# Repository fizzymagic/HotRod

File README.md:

# HotRod
HotRod game controller adapter to USB

## Introduction

This project allows use of a HotRod SE controller with a modern computer.  It also adds considerable 
flexibility, allowing you to remap the HotRod controls to any keys on the keyboard with *no* driver 
configuration on your PC.  Since the device emulates a USB HID keyboard, it will work with any OS that
can use the keyboard, including Windows, Mac OS, and Linux.

## Requirements

Getting the entire thing working requires:

- 32u4-based arduino clone.  I recommand the Pololu A-Star series, but it should work with any 32u4-based board.
  - The Arduino needs a Caterina (or equivalent) bootloader in it.  The Arduino Micro and the A-Star both have this as the default.
- Arduino 1.6.9 or later IDE
- A 6-pin female mini DIN connecter (aka a PS/2 keyboard connector)
- A completed circuit board with the appropriate wires from the DIN connector to the Arduino.  
  You can get a board from OSH Park
- Python 2.7.9 or later.
  - The pyserial library must be installed on the system.

## Getting Started

1. Wire the PS/2 connector to the Arduino, or populate the board.
  - The board design is in the **Hardware/** folder.
  - The board can be obtained from OSH Park [here](https://oshpark.com/shared_projects/7dNfPtaw) 
2. Copy the **HotRod/** folder into the Arduino **libraries/** folder in your Arduino user space. 
   If necessary, you may need to create the **libraries** folder.
3. Copy the **HotRodtoUSB/** folder into the Arduino user space.
4. Copy the **HotRodSetup/** folder into some other place on your computer.  It doesn't really
   matter where.
5. Compile and upload the HotRodtoUSB sketch to the Arduino.
   
## Using the HotRod-to-USB adapter

## Using SetupHotRod.py

This Python script will automatically send commands to the HotRod interface from a file.  You can
save various configurations in command files to quickly load new controller configurations.

You will need Python 2.7.9 or later, with the ```pyserial``` library installed.

### Command Line

<pre>python SetupHotRod.py [-p portname] [-s] [-d] [-r] [cmdFile] ...
         cmdFile  Name of one or more serial commands file(s).  Not required.
         -p  specify serial port, e.g. COM3 for Windows, /dev/ttyS2 for linux and Mac
             if not specified port will be autodetected
         -s  save mapping to EEPROM after processing file
         -d  dump current mapping after processing file
         -r  reset mapping to default before processing file
         -l  reinitialize mapping from EEPROM before processing file</pre>

### Serial Command Set

The following commands are available to be sent to the HotRod interface from SetupHotRod.py; the input file
should consist of one command per line.

- **M sc kb**: Map scan code *sc* to  keyboard key *kb*
  - The scan code and keyboard key can be specified in ways:
    1. As a macro (all macros are defined in HotRod.py)
    2. As a 2-digit hexadecimal number
  - Additionally, the keyboard key can be specified:
    3. As an ASCII character
- **S**: Save the current key mapping to EEPROM
- **R**: Reset the key mapping to the original (in PROGMEM)
- **L**: Load a key mapping from EEPROM
- **D**: Dump the current key mapping
- **?**: Echo "HotRod" to serial port

### Examples:

```M HR_LEFT_JOYSTICK_UP KB_UP_ARROW```  
Maps the left joystick up to the keyboard up arrow.

```M 75 DA```  
Also maps the left joystick up to the keyboard up arrow.

```M HR_LEFT_JOYSTICK_UP i```  
Maps the left joystick up to ASCII 'i'

### Included command files

- SE_MAME_default.hrm
  - Default MAME configuration for 2 players.
- SE_MAME_2joy.hrm
  - Default MAME configuration for 2-joystick games.

## Additional Information

### Pin setup:

```
DIN-6 Pin    Arduino Pin
   1             D2
   3             GND
   4             +5V
   5             D3
```

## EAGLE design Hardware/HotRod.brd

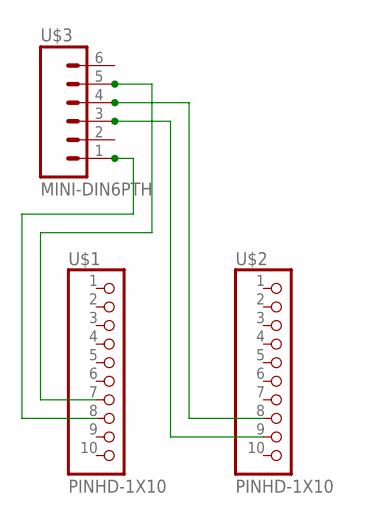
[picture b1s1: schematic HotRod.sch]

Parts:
U$1, U$2: PINHD-1X10; 1X10-BIG
U$3: MINI-DIN6PTH; MINI-DIN6

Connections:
unnamed: U$1.8, U$3.1
unnamed: U$1.7, U$3.5
unnamed: U$2.8, U$3.4
unnamed: U$2.9, U$3.3

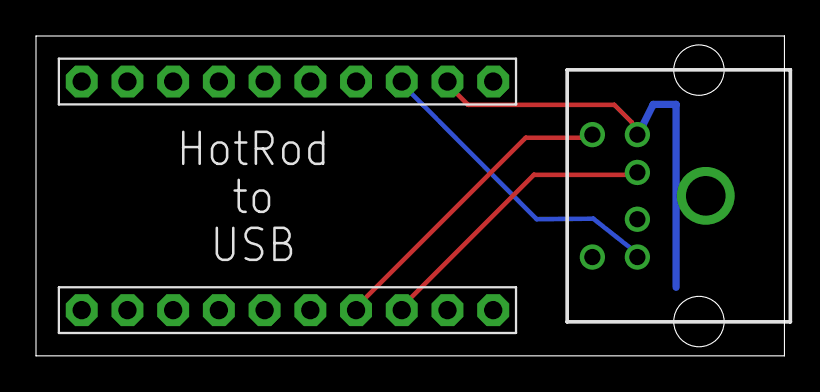
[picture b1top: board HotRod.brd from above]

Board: 2 copper layers, 41.6 x 17.8 mm, 3 parts (0 on the bottom side), 4 nets.

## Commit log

2016-09-04 Added Python to detect HotRod
2016-09-04 Fixed minor bugs
2016-09-04 Minor edit to test git
2016-09-04 Added example MAME deafult file.
2016-09-04 Threads for port detection working. Python to send keymap working.
2016-09-06 Modified Hotrod to allow either uppercase or lowercase characters to be sent.
2016-09-07 Added new map files; cleaned up Arduino project to work with newest IDE.
2016-09-08 Minor modifications to library and timing put into sketch (temporary)
2016-09-09 More additional documentation
2016-09-09 Added Hardware folder
2016-09-26 Added new key files and new key definitions
2016-10-04 Changes to SetupHotRod and minor changes to readme
2016-11-13 Updated documentation
2016-11-13 Finished documentation
2018-02-19 Fixed a couple of unknown bugs

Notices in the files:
parts and their libraries:
SparkFun-Connectors: Licensing: Creative Commons ShareAlike 4.0 International - https://creativecommons.org/licenses/by-sa/4.0
